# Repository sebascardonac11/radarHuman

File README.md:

# radarHuman

Detector de presencia humana con ESP8266-12F y sensor de radar HLK-LD2410B (24 GHz mmWave). Lee los frames UART del sensor y activa un relé cuando detecta presencia continua durante 500 ms. Instalación prevista en pared a 2,5 m de altura en exterior.

---

## Hardware

| Componente | Descripción |
|---|---|
| MCU | ESP8266-12F (160 MHz, 4 MB flash) |
| Sensor | HLK-LD2410B — radar 24 GHz mmWave, detección de movimiento y presencia estática |
| Actuador | Módulo relé 5 V con aislamiento óptico (entrada activa-baja) |
| Driver relé | Transistor NPN BC547 / 2N2222 + resistencia 1 kΩ |

## Conexiones

### LD2410B ↔ ESP8266-12F (SoftwareSerial)

| Pin sensor | GPIO ESP8266 | Pin WeMos D1 Mini | Función |
|---|---|---|---|
| TX | GPIO5 | D1 | Datos sensor → MCU (RX) |
| RX | GPIO14 | D5 | Comandos MCU → sensor (TX) |
| VCC | 3,3 V o 5 V | — | Alimentación |
| GND | GND | — | Tierra común |

### Relé (GPIO4 / D2)

```
GPIO4 ──[1 kΩ]── Base (BC547 / 2N2222)
                 Collector ── IN (módulo relé, activo-bajo)
                 Emitter  ── GND

GPIO4 HIGH  →  transistor ON  →  IN = LOW  →  relé energizado
GPIO4 LOW   →  transistor OFF →  IN = HIGH →  relé desenergizado
```

### Debug / monitor serie

UART0 (GPIO1 TX / GPIO3 RX) se usa para los logs de debug a 115 200 baud, accesible vía USB-serial.

---

## Funcionamiento

1. En `setup()`, `configureSensor()` abre SoftwareSerial a 256 000 baud (default de fábrica) y envía comandos al LD2410B para bajar el baud a 115 200 y reiniciarlo. Si el sensor ya está a 115 200, los comandos llegan corruptos y son ignorados — en ambos casos el sistema arranca en 115 200.
2. El parser de frames (`parseByte`) implementa una máquina de estados de 4 fases sobre el protocolo binario del LD2410B.
3. Cada frame (≈10 Hz) reporta el estado del objetivo en `frameBuf[8]`: `0x00` = ninguno, `0x01` = movimiento, `0x02` = estático, `0x03` = ambos.
4. Al detectar cualquier presencia (`state ≠ 0x00`), se registra `firstDetectedMs`. Tras 500 ms continuos de detección, el relé se activa.
5. `lastDetectedMs` se actualiza en cada frame con presencia. Si pasan 10 s sin detección, el relé se desactiva.

### Parámetros de tiempo

| Constante | Valor | Efecto |
|---|---|---|
| `CONFIRM_MS` | 2 000 ms | Presencia continua mínima para activar el relé |
| `HOLD_MS` | 2 000 ms | Ausencia sostenida para desactivar el relé |

---

## Protocolo UART LD2410B

Frame de reporte (23 bytes, ≈10 Hz):

```
F4 F3 F2 F1  |  0D 00  |  02  AA  [estado]  [dist_mov 2B]  [energía_mov]
[dist_est 2B]  [energía_est]  [dist_det 2B]  55  00  |  F8 F7 F6 F5
```

| Offset | Campo | Valor relevante |
|---|---|---|
| 0–3 | Header | `F4 F3 F2 F1` |
| 4–5 | Data length | `0D 00` (13 bytes) |
| 6 | Data type | `0x02` = reporte periódico |
| 7 | Head | `0xAA` |
| **8** | **Target state** | `0x00` sin objetivo / `≠0x00` presencia |
| 19–22 | End | `F8 F7 F6 F5` |

---

## Build y flash (PlatformIO)

```bash
# Compilar
pio run

# Compilar y flashear
pio run --target upload

# Monitor serie (si el botón de VSCode no responde, usar terminal)
~/.platformio/penv/bin/pio device monitor
```

Plataforma: `espressif8266`, board: `esp12e`, framework: `arduino`, CPU: 160 MHz. Solo se compila `src/main.cpp` (`build_src_filter = +<main.cpp>`).

---

## Documentación oficial

- Google Drive (datasheet, protocolo, herramienta de configuración BLE):
  https://drive.google.com/drive/folders/16zI-fium_BZeP08EyQke0rWp0BJTMvw3
- Protocolo serie detallado: `Doc/HLK-LD2410B human presence detection with BLE/LD2410B Serial communication protocol V1.07.pdf`
- Esquemático y PCB KiCad: `Doc/radarHuman/`

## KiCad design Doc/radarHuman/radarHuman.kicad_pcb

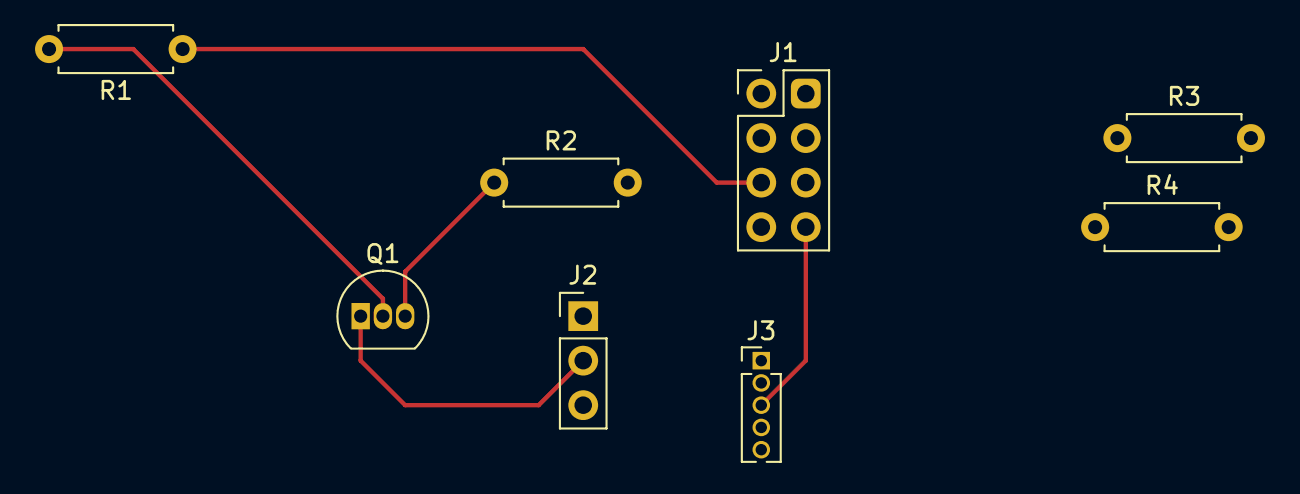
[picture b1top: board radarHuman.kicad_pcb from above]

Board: 2 copper layers, 8 parts (0 on the bottom side), 12 nets.

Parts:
J1: ESP8266-01; PinHeader_2x04_P2.54mm_Vertical
J2: Rele; PinHeader_1x03_P2.54mm_Vertical
J3: LD2410B; PinHeader_1x05_P1.27mm_Vertical
Q1: BC547; TO-92_Inline
R1, R2, R3, R4: 1K; R_Axial_DIN0207_L6.3mm_D2.5mm_P7.62mm_Horizontal

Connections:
-3V3: J1.2, R3.2, R4.2
-5V: J2.3, J3.5
GND: J1.7, J2.1, J3.4, R2.2
unnamed: J1.4 (CH_EN), R3.1
unnamed: J1.5, R1.1
unnamed: J1.6 (Reset), R4.1
unnamed: J2.2, Q1.1 (C)
unnamed: Q1.2 (B), R1.2
unnamed: Q1.3 (E), R2.1
OUT: J1.3, J3.1
UART_RX: J1.8, J3.3
UART_TX: J1.1, J3.2

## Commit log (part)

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2026-05-24 fix: recover from SoftwareSerial byte drops that caused permanent hang
    SoftwareSerial at 115200 baud loses bytes due to ESP8266 background task
    interrupts. When mid-frame bytes were lost the parser got stuck in RD_DATA
    or RD_END forever, consuming subsequent frames as garbage data.
    - Add parser timeout (150 ms): if a non-SYNC state receives no new byte,
    reset to SYNC so the next valid frame is processed normally
    - Call yield() between each byte read so the ESP8266 watchdog and SDK
